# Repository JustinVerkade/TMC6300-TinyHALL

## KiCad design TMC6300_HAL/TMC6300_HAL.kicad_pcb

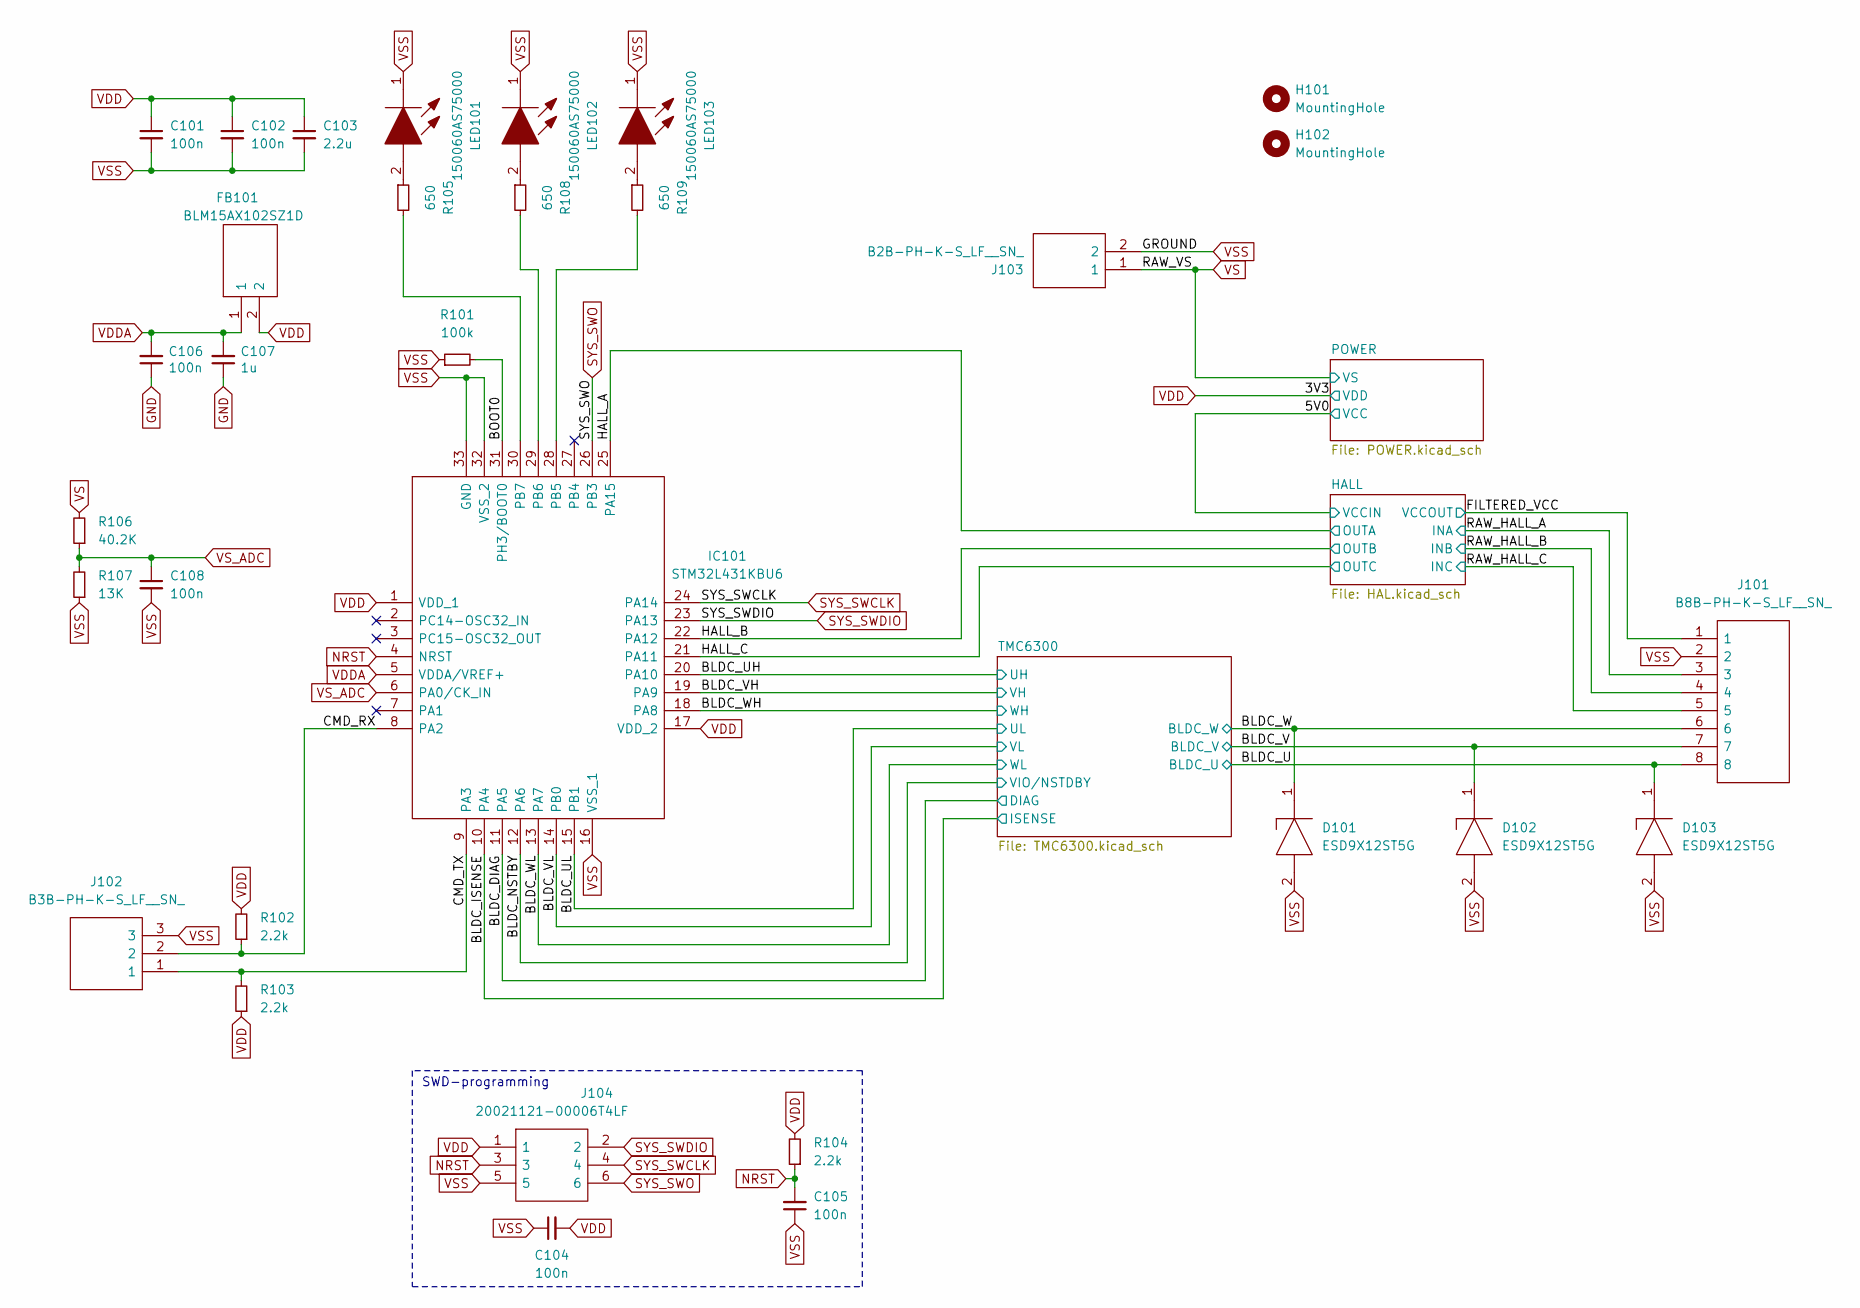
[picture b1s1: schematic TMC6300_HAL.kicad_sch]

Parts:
C101, C102, C104, C105, C106, C108: 100n; C_0402_1005Metric
C103: 2.2u; C_0603_1608Metric
C107: 1u; C_0402_1005Metric
D101, D102, D103: ESD9X12ST5G; SODFL1006X40N; Mouser Part Number 863-ESD9X12ST5G
FB101: BLM15AX102SZ1D; NFZ15SG152SN10B; Mouser Part Number 81-BLM15AX102SZ1D
H101, H102: MountingHole; MountingHole_3.2mm_M3
IC101: STM32L431KBU6; QFN50P500X500X60-33N-D; Mouser Part Number 511-STM32L431KBU6
J101: B8B-PH-K-S_LF__SN_; B8BPHKSLFSN; Manufacturer_Part_Number B8B-PH-K-S(LF)(SN)
J102: B3B-PH-K-S_LF__SN_; SHDR3W50P0X200_1X3_790X450X600P; Manufacturer_Part_Number B3B-PH-K-S(LF)(SN)
J103: B2B-PH-K-S_LF__SN_; SHDR2W50P0X200_1X2_590X450X600P; Manufacturer_Part_Number B2B-PH-K-S(LF)(SN)
J104: 20021121-00006T4LF; HUSSP6W41P127_2X3_381X343X440P; Mouser Part Number 649-221121-00006T4LF
LED101, LED102, LED103: 150060AS75000; LEDC1608X80N; Mouser Part Number 710-150060AS75000
R101: 100k; R_0402_1005Metric
R102, R103, R104: 2.2k; R_0402_1005Metric
R105, R108, R109: 650; R_0402_1005Metric
R106: 40.2K; R_0402_1005Metric
R107: 13K; R_0402_1005Metric

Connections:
/5V0: J101.1; also elsewhere on the board
/BLDC_DIAG: IC101.11 (PA5); also elsewhere on the board
/BLDC_ISENSE: IC101.10 (PA4); also elsewhere on the board
/BLDC_NSTBY: IC101.12 (PA6); also elsewhere on the board
/BLDC_U: D103.1, J101.8; also elsewhere on the board
/BLDC_UH: IC101.20 (PA10); also elsewhere on the board
/BLDC_UL: IC101.15 (PB1); also elsewhere on the board
/BLDC_V: D102.1, J101.7; also elsewhere on the board
/BLDC_VH: IC101.19 (PA9); also elsewhere on the board
/BLDC_VL: IC101.14 (PB0); also elsewhere on the board
/BLDC_W: D101.1, J101.6; also elsewhere on the board
/BLDC_WH: IC101.18 (PA8); also elsewhere on the board
/BLDC_WL: IC101.13 (PA7); also elsewhere on the board
/BOOT0: IC101.31 (PH3/BOOT0), R101.2
/CMD_RX: IC101.8 (PA2), J102.2, R102.1
/CMD_TX: IC101.9 (PA3), J102.1, R103.2
/HALL_A: IC101.25 (PA15); also elsewhere on the board
/HALL_B: IC101.22 (PA12); also elsewhere on the board
/HALL_C: IC101.21 (PA11); also elsewhere on the board
/RAW_HALL_A: J101.3; also elsewhere on the board
/RAW_HALL_B: J101.4; also elsewhere on the board
/RAW_HALL_C: J101.5; also elsewhere on the board
GND: C106.1, C107.1
NRST: C105.2, IC101.4 (NRST), J104.3, R104.1
unnamed: IC101.28 (PB5), R109.2
unnamed: IC101.29 (PB6), R108.2
unnamed: IC101.30 (PB7), R105.2
unnamed: LED101.2, R105.1
unnamed: LED102.2, R108.1
unnamed: LED103.2, R109.1
SYS_SWCLK: IC101.24 (PA14), J104.4
SYS_SWDIO: IC101.23 (PA13), J104.2
SYS_SWO: IC101.26 (PB3), J104.6
VDD: C101.1, C102.1, C103.1, C104.2, FB101.2, IC101.1 (VDD_1), IC101.17 (VDD_2), J104.1, R102.2, R103.1, R104.2; also elsewhere on the board
VDDA: C106.2, C107.2, FB101.1, IC101.5 (VDDA/VREF+)
VS: J103.1, R106.2; also elsewhere on the board
VSS: C101.2, C102.2, C103.2, C104.1, C105.1, C108.2, D101.2, D102.2, D103.2, IC101.16 (VSS_1), IC101.32 (VSS_2), IC101.33 (GND), J101.2, J102.3, J103.2, J104.5, LED101.1, LED102.1, LED103.1, R101.1, R107.1; also elsewhere on the board
VS_ADC: C108.1, IC101.6 (PA0/CK_IN), R106.1, R107.2

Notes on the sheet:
SWD-programming

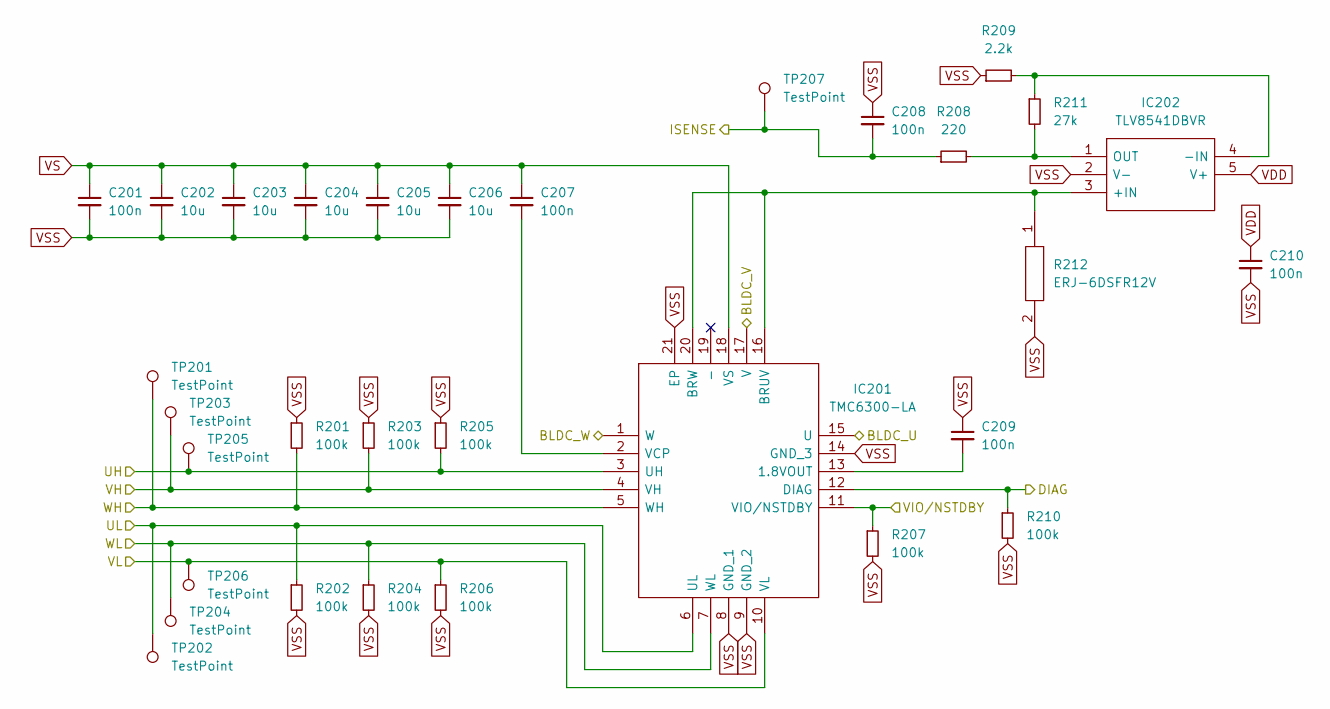
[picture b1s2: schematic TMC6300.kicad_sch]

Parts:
C201, C207, C208, C209, C210: 100n; C_0402_1005Metric
C202, C203, C204, C205, C206: 10u; C_0805_2012Metric
IC201: TMC6300-LA; QFN40P300X300X90-21N; Mouser Part Number 700-TMC6300-LA
IC202: TLV8541DBVR; SOT95P280X145-5N; Mouser Part Number 595-TLV8541DBVR
R201, R202, R203, R204, R205, R206, R207, R210: 100k; R_0402_1005Metric
R208: 220; R_0402_1005Metric
R209: 2.2k; R_0402_1005Metric
R211: 27k; R_0402_1005Metric
R212: ERJ-6DSFR12V; ERJ6_B_BW_R_LW_CW_D; Mouser Part Number 667-ERJ-6DSFR12V
TP201, TP202, TP203, TP204, TP205, TP206, TP207: TestPoint; TestPoint_Pad_D1.0mm

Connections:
/BLDC_DIAG: IC201.12 (DIAG), R210.1; also elsewhere on the board
/BLDC_ISENSE: C208.2, R208.1, TP207.1; also elsewhere on the board
/BLDC_NSTBY: IC201.11 (VIO/NSTDBY), R207.1; also elsewhere on the board
/BLDC_U: IC201.15 (U); also elsewhere on the board
/BLDC_UH: IC201.3 (UH), R205.2, TP205.1; also elsewhere on the board
/BLDC_UL: IC201.6 (UL), R202.1, TP202.1; also elsewhere on the board
/BLDC_V: IC201.17 (V); also elsewhere on the board
/BLDC_VH: IC201.4 (VH), R203.2, TP203.1; also elsewhere on the board
/BLDC_VL: IC201.10 (VL), R206.1, TP206.1; also elsewhere on the board
/BLDC_W: IC201.1 (W); also elsewhere on the board
/BLDC_WH: IC201.5 (WH), R201.2, TP201.1; also elsewhere on the board
/BLDC_WL: IC201.7 (WL), R204.1, TP204.1; also elsewhere on the board
unnamed: C209.2, IC201.13 (1.8VOUT)
unnamed: IC201.16 (BRUV), IC201.20 (BRW), IC202.3 (+IN), R212.1
unnamed: C207.2, IC201.2 (VCP)
unnamed: IC202.4 (-IN), R209.2, R211.1
unnamed: IC202.1 (OUT), R208.2, R211.2
VDD: C210.1, IC202.5 (V+); also elsewhere on the board
VS: C201.1, C202.1, C203.1, C204.1, C205.1, C206.1, C207.1, IC201.18 (VS); also elsewhere on the board
VSS: C201.2, C202.2, C203.2, C204.2, C205.2, C206.2, C208.1, C209.1, C210.2, IC201.8 (GND_1), IC201.9 (GND_2), IC201.14 (GND_3), IC201.21 (EP), IC202.2 (V-), R201.1, R202.2, R203.1, R204.2, R205.1, R206.2, R207.2, R209.1, R210.2, R212.2; also elsewhere on the board

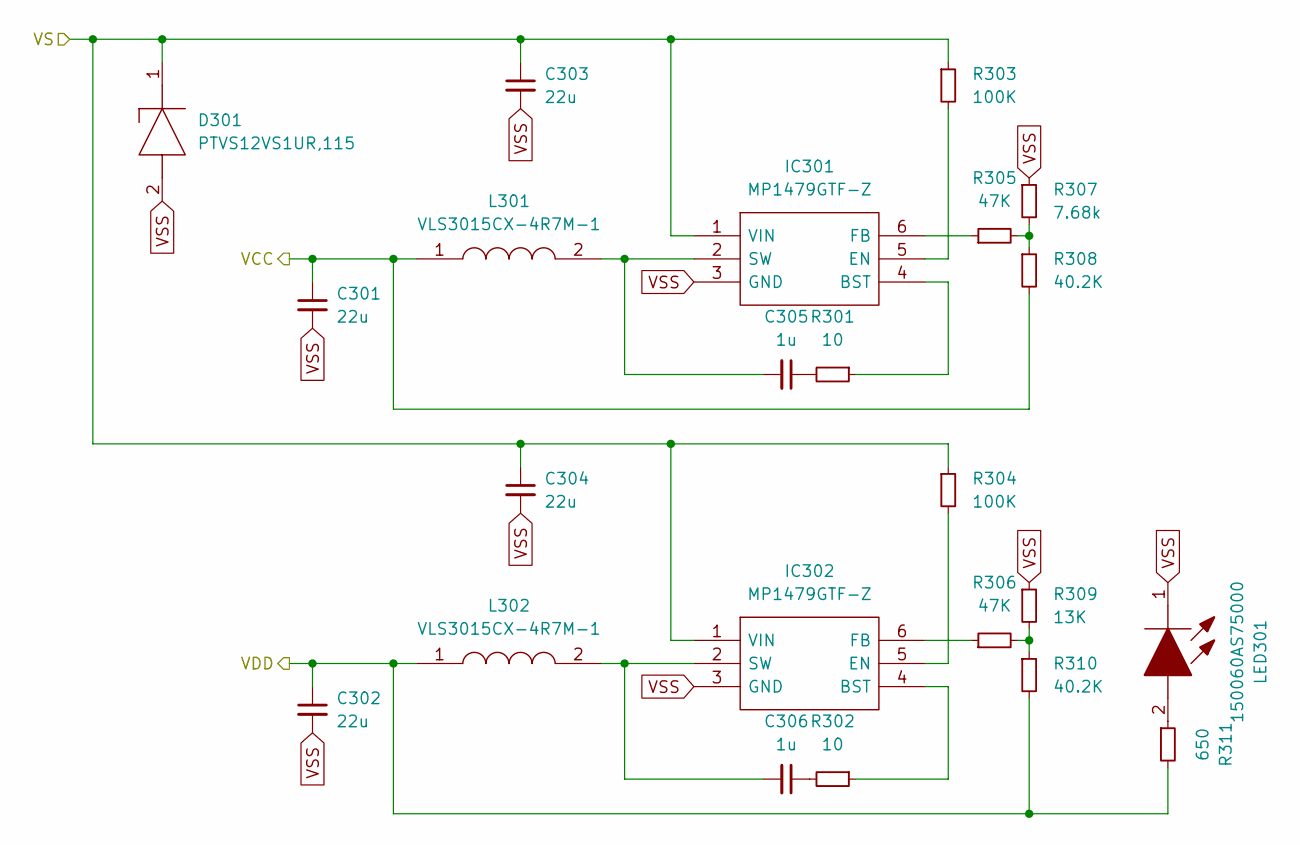
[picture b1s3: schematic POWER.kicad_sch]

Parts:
C301, C302, C303, C304: 22u; C_0805_2012Metric
C305, C306: 1u; C_0603_1608Metric
D301: PTVS12VS1UR,115; SOD123W; Mouser Part Number 771-PTVS12VS1UR115
IC301, IC302: MP1479GTF-Z; MP1479GTFZ; Mouser Part Number 946-MP1479GTF-Z
L301, L302: VLS3015CX-4R7M-1; VLS3015; Manufacturer_Part_Number VLS3015CX-4R7M-1; Mouser Part Number 810-VLS3015CX-4R7M-1
LED301: 150060AS75000; LEDC1608X80N; Mouser Part Number 710-150060AS75000
R301, R302: 10; R_0402_1005Metric
R303, R304: 100K; R_0402_1005Metric
R305, R306: 47K; R_0402_1005Metric
R307: 7.68k; R_0402_1005Metric
R308, R310: 40.2K; R_0402_1005Metric
R309: 13K; R_0402_1005Metric
R311: 650; R_0402_1005Metric

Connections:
/5V0: C301.1, L301.1, R308.2; also elsewhere on the board
unnamed: C305.1, R301.2
unnamed: C306.1, R302.2
unnamed: IC301.4 (BST), R301.1
unnamed: IC301.5 (EN), R303.2
unnamed: IC301.6 (FB), R305.1
unnamed: C305.2, IC301.2 (SW), L301.2
unnamed: IC302.4 (BST), R302.1
unnamed: IC302.5 (EN), R304.2
unnamed: IC302.6 (FB), R306.1
unnamed: C306.2, IC302.2 (SW), L302.2
unnamed: LED301.2, R311.1
unnamed: R305.2, R307.2, R308.1
unnamed: R306.2, R309.2, R310.1
VDD: C302.1, L302.1, R310.2, R311.2; also elsewhere on the board
VS: C303.1, C304.1, D301.1, IC301.1 (VIN), IC302.1 (VIN), R303.1, R304.1; also elsewhere on the board
VSS: C301.2, C302.2, C303.2, C304.2, D301.2, IC301.3 (GND), IC302.3 (GND), LED301.1, R307.1, R309.1; also elsewhere on the board

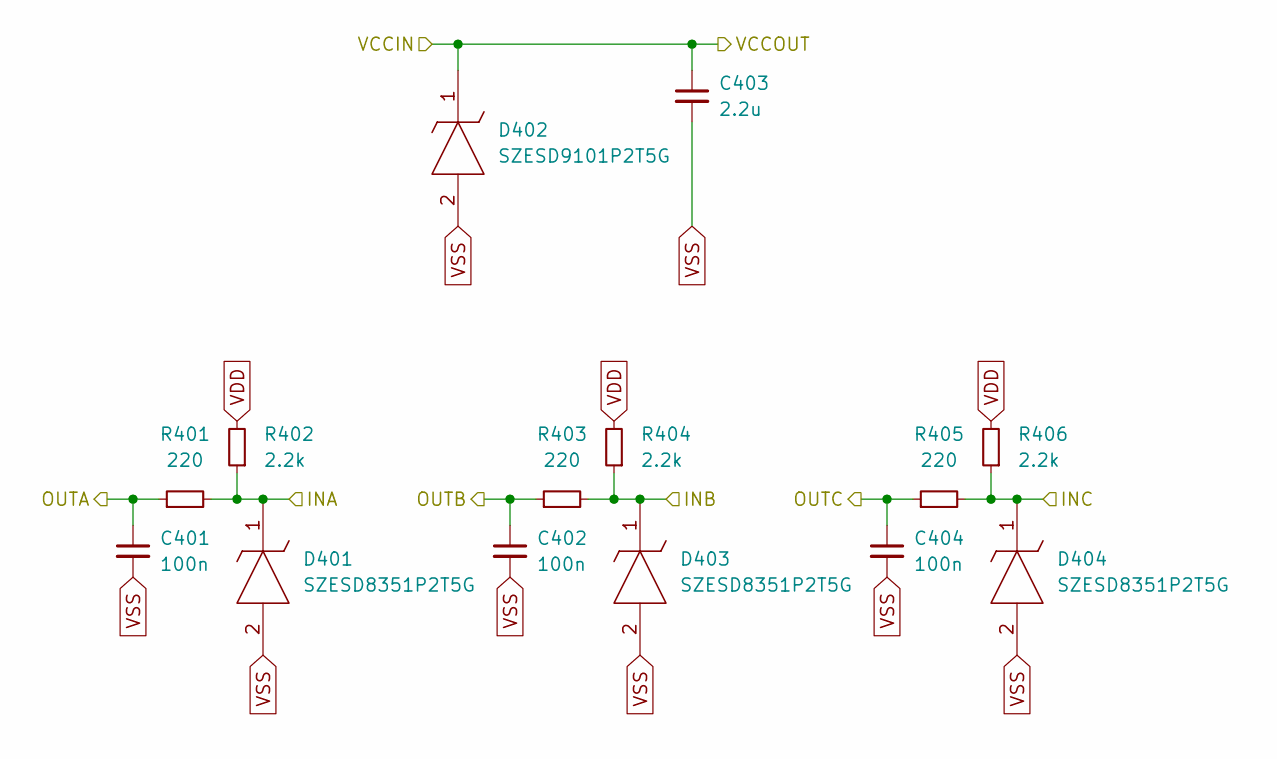
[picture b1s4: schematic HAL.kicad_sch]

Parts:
C401, C402, C404: 100n; C_0402_1005Metric
C403: 2.2u; C_0603_1608Metric
D401, D403, D404: SZESD8351P2T5G; SODFL1006X40N; Mouser Part Number 863-SZESD8351P2T5G
D402: SZESD9101P2T5G; SODFL1006X40N; Mouser Part Number 863-SZESD9101P2T5G
R401, R403, R405: 220; R_0402_1005Metric
R402, R404, R406: 2.2k; R_0402_1005Metric

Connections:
/5V0: C403.1, D402.1; also elsewhere on the board
/HALL_A: C401.1, R401.1; also elsewhere on the board
/HALL_B: C402.1, R403.1; also elsewhere on the board
/HALL_C: C404.1, R405.1; also elsewhere on the board
/RAW_HALL_A: D401.1, R401.2, R402.1; also elsewhere on the board
/RAW_HALL_B: D403.1, R403.2, R404.1; also elsewhere on the board
/RAW_HALL_C: D404.1, R405.2, R406.1; also elsewhere on the board
VDD: R402.2, R404.2, R406.2; also elsewhere on the board
VSS: C401.2, C402.2, C403.2, C404.2, D401.2, D402.2, D403.2, D404.2; also elsewhere on the board

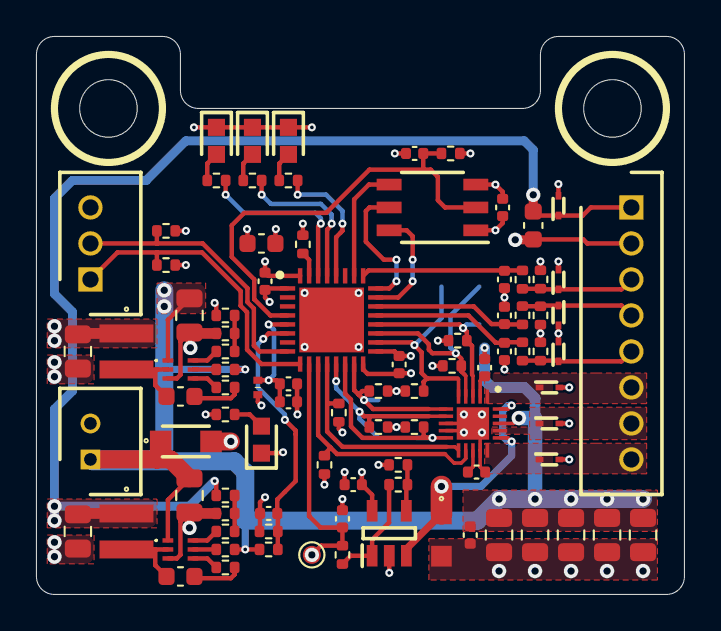
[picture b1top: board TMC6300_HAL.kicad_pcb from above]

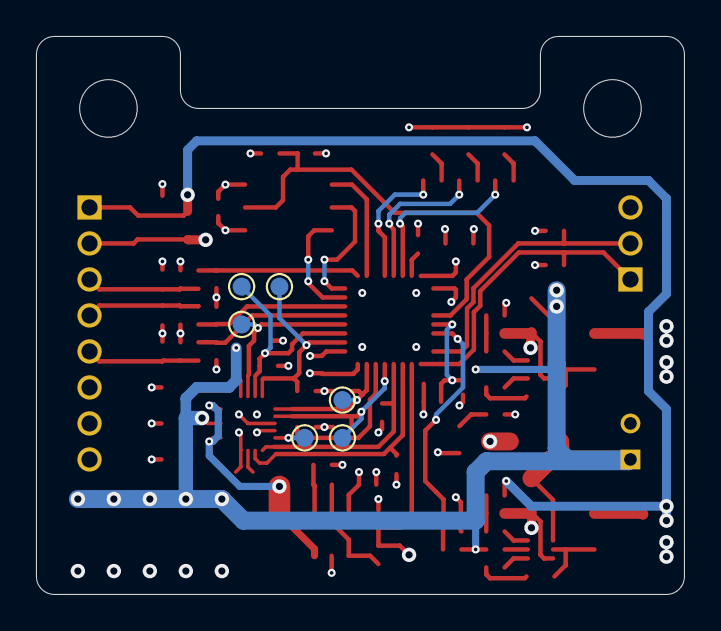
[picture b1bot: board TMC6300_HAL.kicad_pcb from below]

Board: 4 copper layers, 36.0 x 31.0 mm, 99 parts (6 on the bottom side), 56 nets.

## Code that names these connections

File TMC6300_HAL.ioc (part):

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Mcu.Name=STM32L431K(B-C)Ux
Mcu.Package=UFQFPN32
Mcu.UserName=STM32L431KBUx
PA0.GPIOParameters=GPIO_Label
PA0.GPIO_Label=VS_ADC
PA0.Signal=ADCx_IN5
PA10.GPIOParameters=GPIO_Label
PA10.GPIO_Label=BLDC_UH
PA10.Signal=S_TIM1_CH3
PA11.GPIOParameters=GPIO_Label,GPIO_ModeDefaultEXTI
PA11.GPIO_Label=HAL_C
PA11.GPIO_ModeDefaultEXTI=GPIO_MODE_IT_RISING_FALLING
PA11.Signal=GPXTI11
PA12.GPIOParameters=GPIO_Label,GPIO_ModeDefaultEXTI
PA12.GPIO_Label=HAL_B
PA12.GPIO_ModeDefaultEXTI=GPIO_MODE_IT_RISING_FALLING
PA12.Signal=GPXTI12
PA13\ (JTMS-SWDIO).Mode=Trace_Asynchronous_SW
PA13\ (JTMS-SWDIO).Signal=SYS_JTMS-SWDIO
PA14\ (JTCK-SWCLK).Mode=Trace_Asynchronous_SW
PA14\ (JTCK-SWCLK).Signal=SYS_JTCK-SWCLK
PA15\ (JTDI).GPIOParameters=GPIO_Label,GPIO_ModeDefaultEXTI
PA15\ (JTDI).GPIO_Label=HAL_A
PA15\ (JTDI).GPIO_ModeDefaultEXTI=GPIO_MODE_IT_RISING_FALLING
PA15\ (JTDI).Signal=GPXTI15
PA2.GPIOParameters=GPIO_Speed,GPIO_Label
PA2.GPIO_Label=COMMAND_TX
PA2.GPIO_Speed=GPIO_SPEED_FREQ_MEDIUM
PA2.Mode=Asynchronous
PA2.Signal=USART2_TX
PA3.GPIOParameters=GPIO_Speed,GPIO_Label
PA3.GPIO_Label=COMMAND_RX
PA3.GPIO_Speed=GPIO_SPEED_FREQ_MEDIUM
PA3.Mode=Asynchronous
PA3.Signal=USART2_RX
PA4.GPIOParameters=GPIO_Label
PA4.GPIO_Label=BLDC_ISENSE
PA4.Signal=ADCx_IN9
PA5.GPIOParameters=GPIO_Label
PA5.GPIO_Label=BLDC_DIAG
PA5.Signal=GPXTI5
PA6.GPIOParameters=PinState,GPIO_Label
PA6.GPIO_Label=BLDC_NSTDBY
PA6.PinState=GPIO_PIN_SET
PA6.Signal=GPIO_Output
PA7.GPIOParameters=GPIO_Label
PA7.GPIO_Label=BLDC_WL
PA7.Mode=PWM Generation1 CH1 CH1N
PA7.Signal=TIM1_CH1N
PA8.GPIOParameters=GPIO_Label
PA8.GPIO_Label=BLDC_WH
PA8.Signal=S_TIM1_CH1
PA9.GPIOParameters=GPIO_Label
PA9.GPIO_Label=BLDC_VH
PA9.Signal=S_TIM1_CH2
PB0.GPIOParameters=GPIO_Label
PB0.GPIO_Label=BLDC_VL
PB0.Mode=PWM Generation2 CH2 CH2N
PB0.Signal=TIM1_CH2N
PB1.GPIOParameters=GPIO_Label
PB1.GPIO_Label=BLDC_UL
PB1.Mode=PWM Generation3 CH3 CH3N
PB1.Signal=TIM1_CH3N
PB3\ (JTDO-TRACESWO).Mode=Trace_Asynchronous_SW
PB3\ (JTDO-TRACESWO).Signal=SYS_JTDO-SWO
PB5.GPIOParameters=GPIO_Label
PB5.GPIO_Label=LED2
PB5.Signal=GPIO_Output
PB6.GPIOParameters=GPIO_Label
PB6.GPIO_Label=LED1
PB6.Signal=GPIO_Output
PB7.GPIOParameters=GPIO_Label
PB7.GPIO_Label=LED0
PB7.Signal=GPIO_Output
RCC.HSE_VALUE=8000000
RCC.SYSCLKFreq_VALUE=80000000
RCC.SYSCLKSource=RCC_SYSCLKSOURCE_PLLCLK
board=custom

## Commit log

2024-03-12 Added hardware files
2024-05-30 Version used with Lencon blower.
2024-11-14 Cleanup local to github
